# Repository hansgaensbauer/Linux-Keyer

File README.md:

# Linux-Keyer
An automatic CW keyer build around the [SimpleSBC](https://github.com/hansgaensbauer/SimpleSBC).

## Features
- 2 Key/Paddle inputs (both keys and paddles supported on both inputs)
- Automatic detection of key wiring
- PTT and Key outputs
- Internal and external speaker support
- Network connectivity (10/100)
- Linux!

<table>
  <tr>
    <td></td>
    <td>
  </tr>
</table>

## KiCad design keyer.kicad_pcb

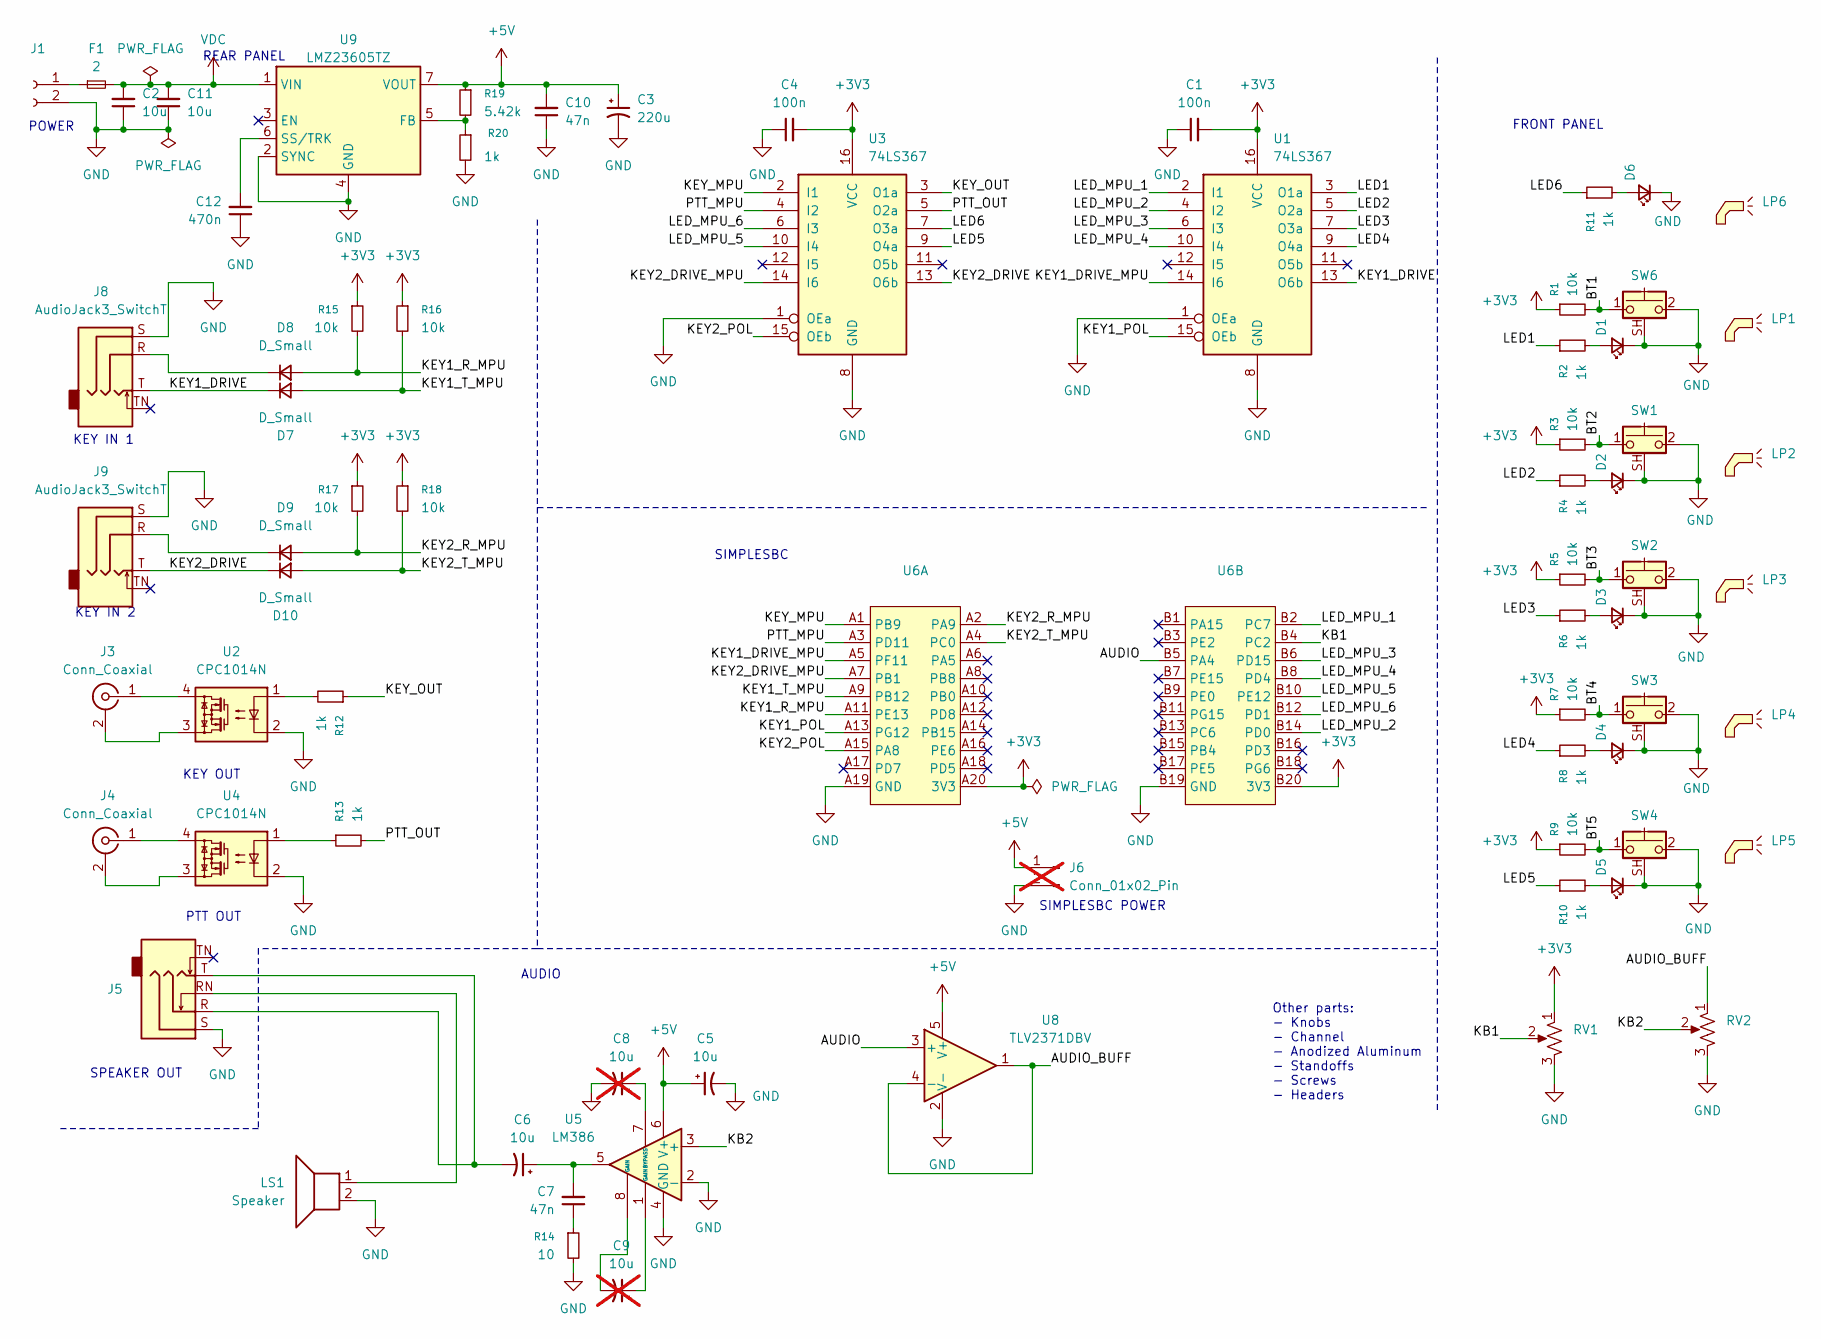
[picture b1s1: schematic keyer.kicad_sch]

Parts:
C1, C4: 100n; C_0603_1608Metric; Digikey PN 399-C0603C104K5RACTUCT-ND
C2, C5, C6, C11: 10u; C_1206_3216Metric; Digikey PN 1276-1804-1-ND
C3: 220u; CP_Elec_6.3x7.7; Digikey PN 732-8422-1-ND
C7, C10: 47n; C_0603_1608Metric; Digikey PN 490-5854-1-ND
C8, C9: 10u; C_1206_3216Metric; Digikey PN 1276-1804-1-ND; not fitted
C12: 470n; C_0603_1608Metric; Digikey PN 490-3291-1-ND
D1, D2, D3, D4, D5, D6: LED_Small; LED_0603_1608Metric
D7, D8, D9, D10: D_Small; D_SOD-323; Digikey PN 1N4148WXTPMSCT-ND
F1: 2; Fuse_1206_3216Metric; Digikey PN 2315-SBF32202ASTPCT-ND
J1: Conn_01x02_Socket; Powerpole_1x2; Digikey PN 2243-ASMPR45-1X2-RK-ND
J3, J4: Conn_Coaxial; CUI_RCJ-041; Digikey PN CP-1418-ND
J5: AudioJack3_SwitchTR; Jack_3.5mm_CUI_SJ1-3535NG_Horizontal; Digikey PN CP1-3535NG-ND
J6: Conn_01x02_Pin; PinHeader_1x02_P2.54mm_Vertical; not fitted
J8, J9: AudioJack3_SwitchT; SJ-63063B; Digikey PN 2223-SJ-63063B-ND
LP1, LP2, LP3, LP4, LP5, LP6: SLP3-500-450-R; Digikey PN SLP3-500-450-R-ND
LS1: Speaker; JST_XH_B2B-XH-AM_1x02_P2.50mm_Vertical; Digikey PN 2223-CMS-30205-158L120-67-ND
R1, R3, R5, R7, R9, R15, R16, R17, R18: 10k; R_0603_1608Metric; Digikey PN RMCF0603FT10K0CT-ND
R2, R4, R6, R8, R10, R11, R12, R13, R20: 1k; R_0603_1608Metric; Digikey PN 541-1.00KHCT-ND
R14: 10; R_0603_1608Metric; Digikey PN RMCF0603FT10R0CT-ND
R19: 5.42k; R_0603_1608Metric; Digikey PN 2019-RN73R1JTTD5421B25CT-ND
RV1, RV2: R_Potentiometer_US; POT_PTN16-A01120K1B1; Digikey PN 2223-PTN16-A01120K1B1-ND
SW1, SW2, SW3, SW4, SW6: SW_Push_Shielded; 4312560837X6; Digikey PN 431256083716-ND
U1, U3: 74LS367; SOP-16_3.9x9.9mm_P1.27mm; Digikey PN 296-14849-1-ND
U2, U4: CPC1014N; SOP-4_3.8x4.1mm_P2.54mm; Digikey PN CPC1014N-ND
U5: LM386; SOIC-8_3.9x4.9mm_P1.27mm; Digikey PN LM386MX-1/NOPBCT-ND
U6: SimpleSBC; Digikey PN 1212-1247-ND
U8: TLV2371DBV; SOT-23-5; Digikey PN 296-26785-1-ND
U9: LMZ23605TZ; Texas_NDW-7_TabPin4; Digikey PN 296-LMZ23605TZX/NOPBCT-ND

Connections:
+3V3: C1.2, C4.2, R1.1, R3.1, R5.1, R7.1, R9.1, R15.1, R16.1, R17.1, R18.1, RV1.1, U1.16 (VCC), U3.16 (VCC), U6.A20 (3V3), U6.B20 (3V3)
+5V: C3.1, C5.1, C10.2, J6.1, R19.1, U5.6 (V+), U8.5 (V+), U9.7 (VOUT)
/AUDIO: U6.B5 (PA4), U8.3 (+)
/AUDIO_BUFF: RV2.1, U8.1, U8.4 (-)
/BT1: R1.2, SW6.1
/BT2: R3.2, SW1.1
/BT3: R5.2, SW2.1
/BT4: R7.2, SW3.1
/BT5: R9.2, SW4.1
/KB1: RV1.2, U6.B4 (PC2)
/KB2: RV2.2, U5.3 (+)
/KEY1_DRIVE: D7.1 (K), J8.T, U1.13 (O6b)
/KEY1_DRIVE_MPU: U1.14 (I6), U6.A5 (PF11)
/KEY1_POL: U1.15 (OEb), U6.A13 (PG12)
/KEY1_R_MPU: D8.2 (A), R15.2, U6.A11 (PE13)
/KEY1_T_MPU: D7.2 (A), R16.2, U6.A9 (PB12)
/KEY2_DRIVE: D10.1 (K), J9.T, U3.13 (O6b)
/KEY2_DRIVE_MPU: U3.14 (I6), U6.A7 (PB1)
/KEY2_POL: U3.15 (OEb), U6.A15 (PA8)
/KEY2_R_MPU: D9.2 (A), R17.2, U6.A2 (PA9)
/KEY2_T_MPU: D10.2 (A), R18.2, U6.A4 (PC0)
/KEY_MPU: U3.2 (I1), U6.A1 (PB9)
/KEY_OUT: R12.1, U3.3 (O1a)
/LED1: R2.1, U1.3 (O1a)
/LED2: R4.1, U1.5 (O2a)
/LED3: R6.1, U1.7 (O3a)
/LED4: R8.1, U1.9 (O4a)
/LED5: R10.1, U3.9 (O4a)
/LED6: R11.1, U3.7 (O3a)
/LED_MPU_1: U1.2 (I1), U6.B2 (PC7)
/LED_MPU_2: U1.4 (I2), U6.B14 (PD0)
/LED_MPU_3: U1.6 (I3), U6.B6 (PD15)
/LED_MPU_4: U1.10 (I4), U6.B8 (PD4)
/LED_MPU_5: U3.10 (I4), U6.B10 (PE12)
/LED_MPU_6: U3.6 (I3), U6.B12 (PD1)
/PTT_MPU: U3.4 (I2), U6.A3 (PD11)
/PTT_OUT: R13.2, U3.5 (O2a)
GND: C1.1, C2.1, C3.2, C4.1, C5.2, C8.2, C10.1, C11.1, C12.1, D1.1 (K), D2.1 (K), D3.1 (K), D4.1 (K), D5.1 (K), D6.1 (K), J1.2, J5.S, J6.2, J8.S, J9.S, LS1.2, R14.2, R20.2, RV1.3, RV2.3, SW1.2, SW1.SH (B), SW2.2, SW2.SH (B), SW3.2, SW3.SH (B), SW4.2, SW4.SH (B), SW6.2, SW6.SH (B), U1.1 (OEa), U1.8 (GND), U2.2, U3.1 (OEa), U3.8 (GND), U4.2, U5.2 (-), U5.4 (GND), U6.A19 (GND), U6.B19 (GND), U8.2 (V-), U9.2 (SYNC), U9.4 (GND)
unnamed: C6.1, C7.2, U5.5
unnamed: C6.2, J5.R, J5.T
unnamed: C7.1, R14.1
unnamed: C9.1, U5.1 (GAIN)
unnamed: C9.2, U5.8 (GAIN)
unnamed: D1.2 (A), R2.2
unnamed: D2.2 (A), R4.2
unnamed: D3.2 (A), R6.2
unnamed: D4.2 (A), R8.2
unnamed: D5.2 (A), R10.2
unnamed: D6.2 (A), R11.2
unnamed: D8.1 (K), J8.R
unnamed: D9.1 (K), J9.R
unnamed: F1.1, J1.1
unnamed: J3.2 (Ext), U2.3
unnamed: J3.1 (In), U2.4
unnamed: J4.2 (Ext), U4.3
unnamed: J4.1 (In), U4.4
unnamed: J5.RN, LS1.1
unnamed: R12.2, U2.1
unnamed: R13.1, U4.1
unnamed: C8.1, U5.7 (BYPASS)
unnamed: R19.2, R20.1, U9.5 (FB)
unnamed: C12.2, U9.6 (SS/TRK)
VDC: C2.2, C11.2, F1.2, U9.1 (VIN)

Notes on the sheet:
SPEAKER OUT
SIMPLESBC POWER
KEY IN 1
FRONT PANEL
KEY OUT
SIMPLESBC
KEY IN 2
REAR PANEL
POWER
PTT OUT
Other parts: - Knobs - Channel - Anodized Aluminum - Standoffs - Screws - Headers
AUDIO

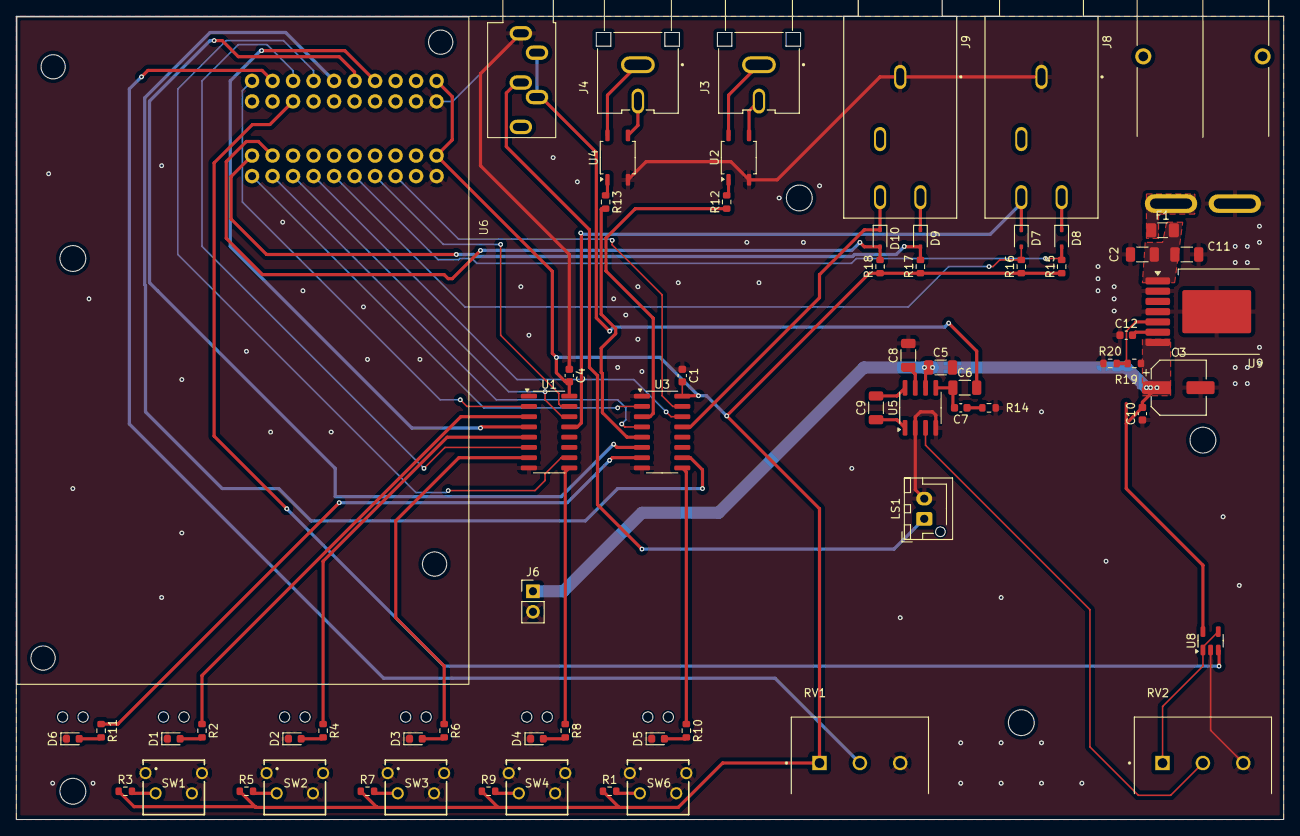
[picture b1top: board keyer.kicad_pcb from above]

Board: 2 copper layers, 156.9 x 99.4 mm, 72 parts (0 on the bottom side), 63 nets.

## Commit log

2025-12-09 Add Photos and Case Drawings
